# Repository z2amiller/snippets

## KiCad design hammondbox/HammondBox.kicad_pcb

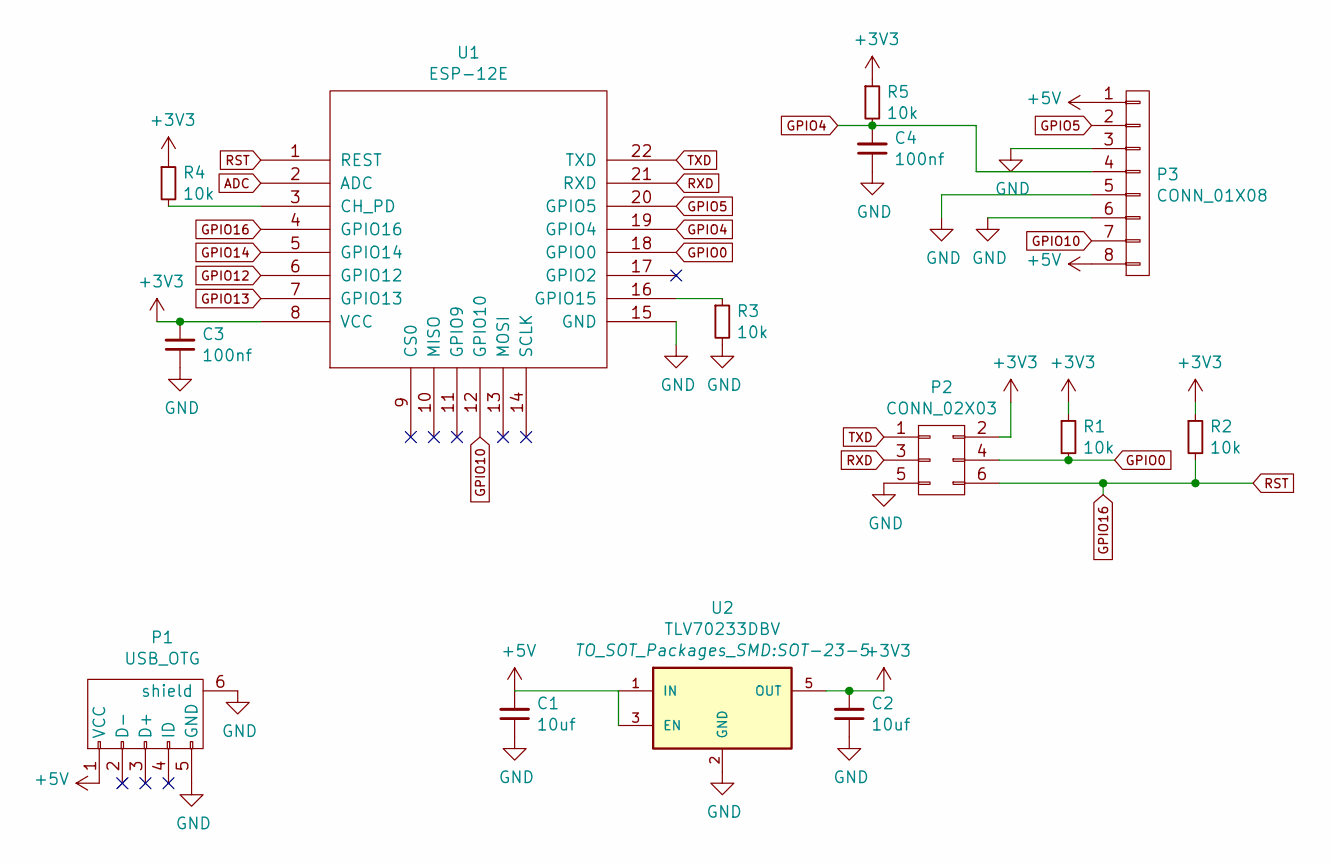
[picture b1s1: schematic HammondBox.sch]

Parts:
C1, C2: 10uf; C_0805_HandSoldering
C3, C4: 100nf; C_0603_HandSoldering
P1: USB_OTG; USB_Micro-B
P2: CONN_02X03; Pin_Header_Straight_2x03
P3: CONN_01X08; Pin_Header_Straight_1x08
R1, R2, R3, R4, R5: 10k; R_0603_HandSoldering
U1: ESP-12E
U2: TLV70233DBV; SOT-23-5

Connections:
+3V3: C2.2, C3.2, P2.2, R1.1, R2.1, R4.1, R5.1, U1.8 (VCC), U2.5 (OUT)
+5V: C1.2, P1.1 (VCC), P3.1, P3.8, U2.1 (IN), U2.3 (EN)
ADC: U1.2 (ADC)
GND: C1.1, C2.1, C3.1, C4.1, P1.5 (GND), P1.6 (shield), P2.5, P3.3, P3.5, P3.6, R3.2, U1.15 (GND), U2.2 (GND)
GPIO0: P2.4, R1.2, U1.18 (GPIO0)
GPIO4: C4.2, P3.4, R5.2, U1.19 (GPIO4)
GPIO5: P3.2, U1.20 (GPIO5)
GPIO10: P3.7, U1.12 (GPIO10)
GPIO12: U1.6 (GPIO12)
GPIO13: U1.7 (GPIO13)
GPIO14: U1.5 (GPIO14)
GPIO16: P2.6, R2.2, U1.1 (REST), U1.4 (GPIO16)
unnamed: R3.1, U1.16 (GPIO15)
unnamed: R4.2, U1.3 (CH_PD)
RXD: P2.3, U1.21 (RXD)
TXD: P2.1, U1.22 (TXD)

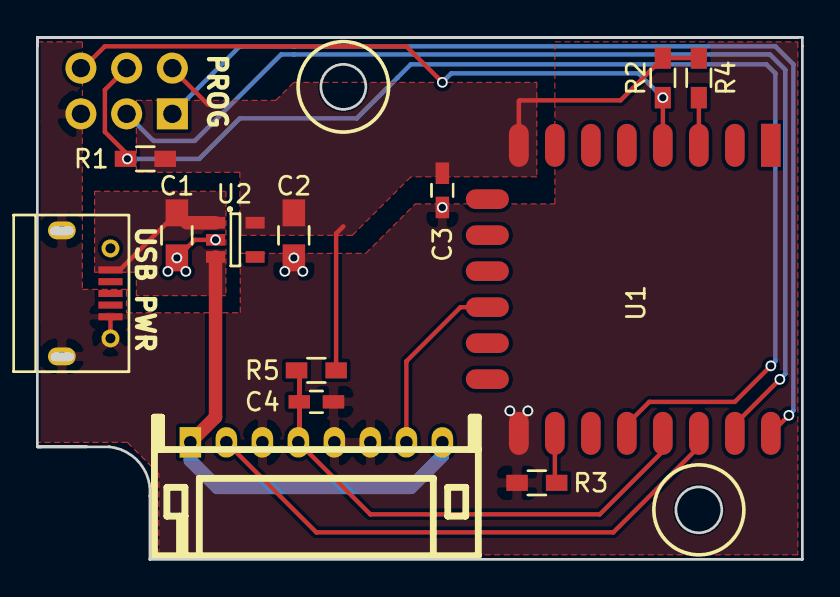
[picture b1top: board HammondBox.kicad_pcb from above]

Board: 2 copper layers, 42.1 x 28.7 mm, 14 parts (1 on the bottom side), 12 nets.

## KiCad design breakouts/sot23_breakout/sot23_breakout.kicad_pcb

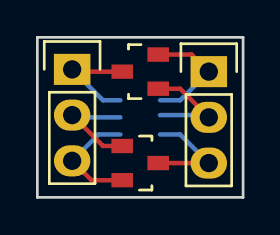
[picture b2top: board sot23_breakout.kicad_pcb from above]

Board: 2 copper layers, 11.4 x 8.9 mm, 5 parts (1 on the bottom side), 6 nets.

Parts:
IC1: ATTINY10-TS; SOT-23-6
P1, P2: CONN_01X03; Pin_Header_Straight_1x03
Q1, Q2: MMBT3904; SOT-23

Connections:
LEFT_1: IC1.3, P1.1, Q2.3
LEFT_2: IC1.2, P1.2, Q1.1
LEFT_3: IC1.1, P1.3, Q1.2
RIGHT_1: IC1.4, P2.1, Q2.2
RIGHT_2: IC1.5, P2.2, Q2.1
RIGHT_3: IC1.6, P2.3, Q1.3

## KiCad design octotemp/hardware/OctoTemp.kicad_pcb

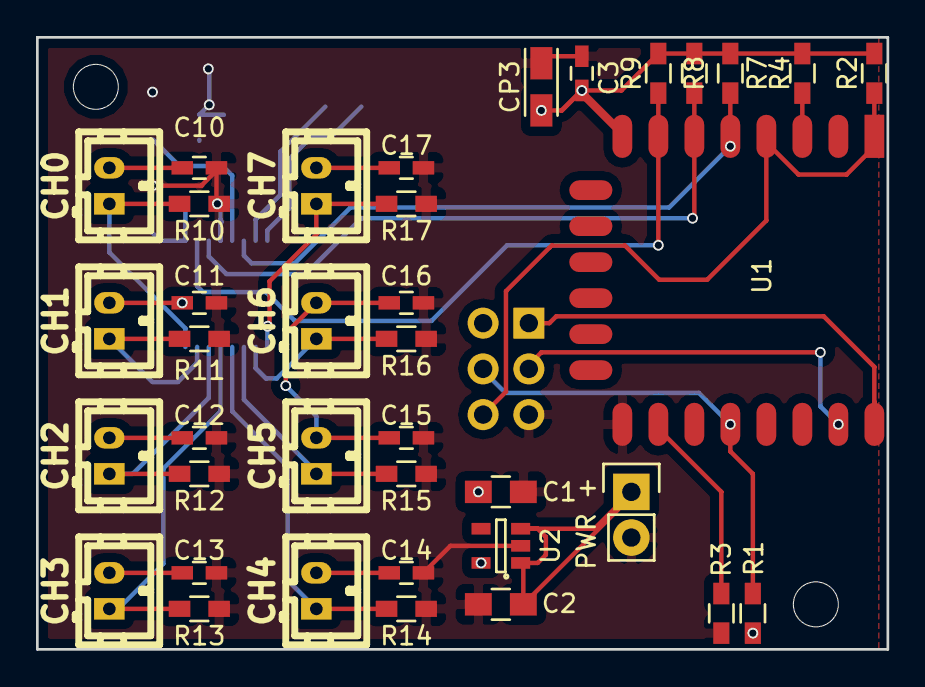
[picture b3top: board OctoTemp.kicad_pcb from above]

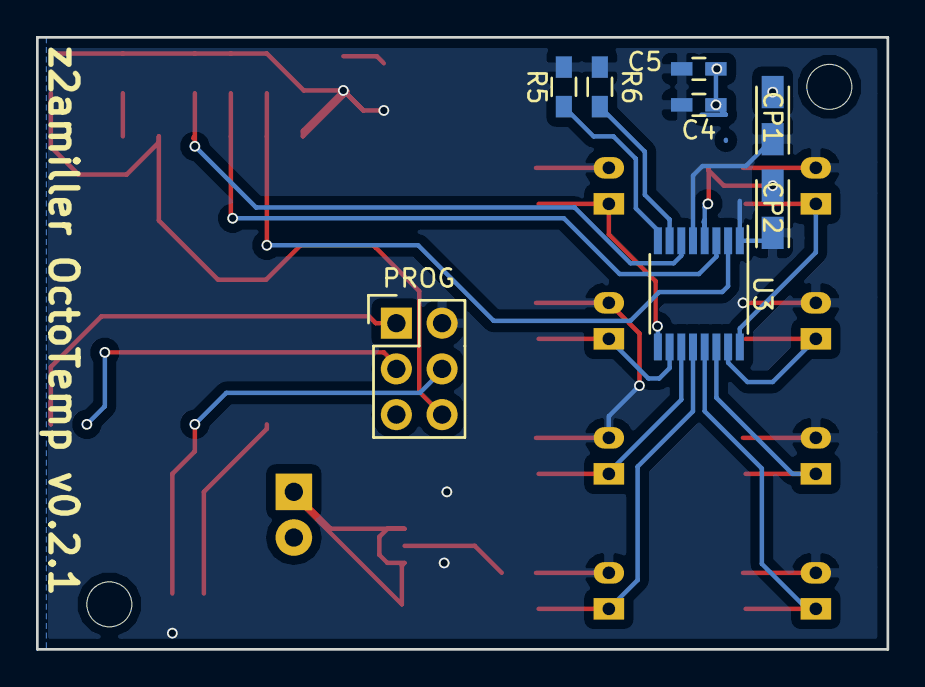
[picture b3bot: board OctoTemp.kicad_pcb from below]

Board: 2 copper layers, 47.2 x 34.0 mm, 46 parts (8 on the bottom side), 22 nets.

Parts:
C1, C2: 10uf; C_0805_HandSoldering
C3, C4, C5, C10, C11, C12, C13, C14, C15, C16, C17: 100nf; C_0603_HandSoldering
CH0, CH1, CH2, CH3, CH4, CH5, CH6, CH7: CONN_01X02; b2b-ph-kl
CP1, CP2, CP3: 1uf; TantalC_SizeA_EIA-3216_Reflow
PROG: CONN_02X03; Pin_Header_Straight_2x03
PWR +: CONN_01X02; Pin_Header_Straight_1x02
R1, R2, R3, R4, R5, R6, R7, R8, R9, R10, R11, R12, R13, R14, R15, R16, R17: 10k; R_0603_HandSoldering
U1: ESP-12E
U2: SPX3819M5; SOT-23-5
U3: ADC128D818; TSSOP-16_4.4x5mm_Pitch0.65mm

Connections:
+5V: C2.2, PWR +.1, U2.1, U2.3
ADC_GND: C1.2, C2.1, C3.1, C4.1, C5.2, C10.1, C11.1, C12.1, C13.1, C14.1, C15.1, C16.1, C17.1, CP1.2, CP2.2, CP3.1, PROG.5, PWR +.2, R3.2, R10.2, R11.2, R12.2, R13.2, R14.2, R15.2, R16.2, R17.2, U1.15, U2.2, U3.4
ADC_INT: R7.2, U1.5, U3.6
ADC_VIN: C1.1, C3.2, C4.2, C5.1, C10.2, C11.2, C12.2, C13.2, C14.2, C15.2, C16.2, C17.2, CH0.2, CH1.2, CH2.2, CH3.2, CH4.2, CH5.2, CH6.2, CH7.2, CP1.1, CP2.1, CP3.2, PROG.2, R1.1, R2.1, R4.1, R5.1, R6.1, R7.1, R8.1, R9.1, U1.8, U2.5, U3.1, U3.5
ESP_RST: PROG.6, R2.2, U1.1, U1.4
ESP_RXD: PROG.3, U1.21
ESP_TXD: PROG.1, U1.22
GPIO0: PROG.4, R1.2, U1.18
IN0: CH0.1, R10.1, U3.16
IN1: CH1.1, R11.1, U3.15
IN2: CH2.1, R12.1, U3.14
IN3: CH3.1, R13.1, U3.13
IN4: CH4.1, R14.1, U3.12
IN5: CH5.1, R15.1, U3.11
IN6: CH6.1, R16.1, U3.10
IN7: CH7.1, R17.1, U3.9
unnamed: R3.1, U1.16
unnamed: R4.2, U1.3
unnamed: R5.2, U3.8
unnamed: R6.2, U3.7
SCL: R8.2, U1.6, U3.3
SDA: R9.2, U1.7, U3.2

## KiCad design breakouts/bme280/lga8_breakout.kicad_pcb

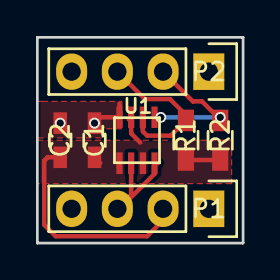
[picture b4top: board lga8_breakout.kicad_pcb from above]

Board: 2 copper layers, 11.4 x 11.4 mm, 7 parts (0 on the bottom side), 4 nets.

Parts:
C1, C2: 100nf; C_0603_HandSoldering
P1, P2: CONN_01X04; Pin_Header_Straight_1x04
R1, R2: 10k; R_0603_HandSoldering
U1: BME280; FGA8

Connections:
+3V3: C1.1, C2.2, P1.2, R1.1, R2.1, U1.2, U1.6, U1.8
GND: C1.2, C2.1, P1.3, U1.1, U1.5, U1.7
unnamed: P2.2, R2.2, U1.4
unnamed: P2.3, R1.2, U1.3

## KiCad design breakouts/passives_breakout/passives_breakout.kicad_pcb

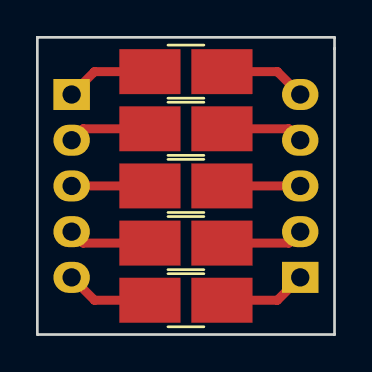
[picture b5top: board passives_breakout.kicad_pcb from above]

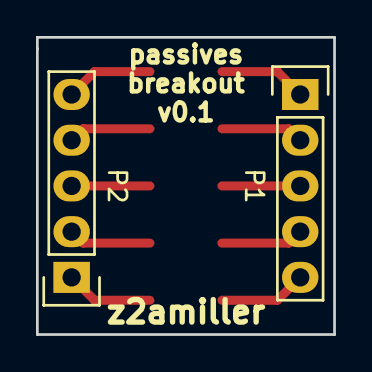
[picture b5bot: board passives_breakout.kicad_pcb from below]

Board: 2 copper layers, 16.5 x 16.5 mm, 7 parts (2 on the bottom side), 10 nets.

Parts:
P1, P2: CONN_01X05; Pin_Header_Straight_1x05
R1, R2, R3, R4, R5: R_Small; R_1210_HandSoldering

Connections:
unnamed: P1.1, R5.2
unnamed: P1.2, R4.2
unnamed: P1.3, R3.2
unnamed: P1.4, R2.2
unnamed: P1.5, R1.2
unnamed: P2.1, R1.1
unnamed: P2.2, R2.1
unnamed: P2.3, R3.1
unnamed: P2.4, R4.1
unnamed: P2.5, R5.1

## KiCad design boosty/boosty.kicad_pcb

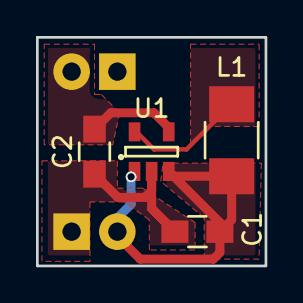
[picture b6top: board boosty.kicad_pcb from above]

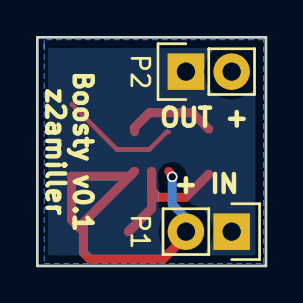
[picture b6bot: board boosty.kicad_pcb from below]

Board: 2 copper layers, 12.7 x 12.7 mm, 6 parts (2 on the bottom side), 4 nets.

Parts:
C1, C2: 10uF; C_0805_HandSoldering
L1: 4.7uH; R_1210_HandSoldering
P1, P2: CONN_01X02; Pin_Header_Straight_1x02
U1: XC9140; SOT-23-5

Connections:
+5V: C2.1, P2.2, U1.4
+BATT: C1.1, L1.1, P1.2, U1.1, U1.3
GND: C1.2, C2.2, P1.1, P2.1, U1.2
unnamed: L1.2, U1.5

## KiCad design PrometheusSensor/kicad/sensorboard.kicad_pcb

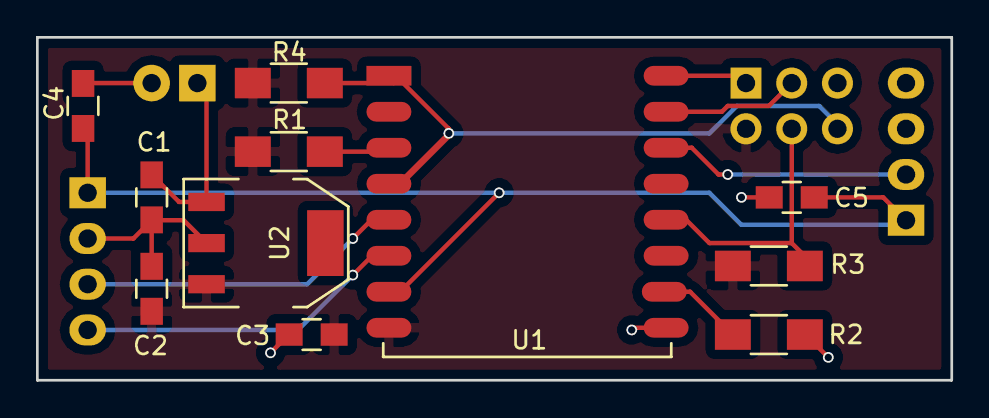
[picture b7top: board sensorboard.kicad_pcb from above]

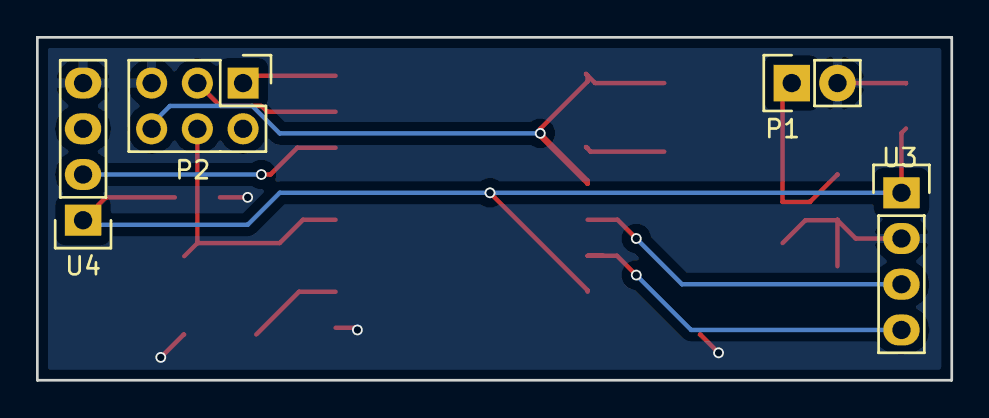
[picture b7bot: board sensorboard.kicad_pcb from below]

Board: 2 copper layers, 50.8 x 19.0 mm, 15 parts (4 on the bottom side), 13 nets.

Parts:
C1, C2: 10uf; C_0805_HandSoldering
C3, C4, C5: 100nf; C_0805_HandSoldering
P1: PWR; Pin_Header_Straight_1x02
P2: PROG; Pin_Header_Straight_2x03
R1, R2, R3, R4: 10k; R_1206_HandSoldering
U1: ESP-07v2; ESP-12
U2: TC1262; SOT-223
U3: BMP180_board; Pin_Header_Straight_1x04
U4: DHT22; Pin_Header_Straight_1x04

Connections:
+3.3VP: C4.2, C5.2, U1.7, U3.1, U4.1
+3V3: C2.1, C3.1, P2.2, R1.1, R3.1, R4.1, U1.8, U2.3
+6V: C1.1, P1.1, U2.1
CH_PD: R1.2, U1.3
GND: C1.2, C2.2, C3.2, C4.1, C5.1, P1.2, P2.5, R2.2, U1.9, U2.2, U3.2, U4.4
GPIO0: P2.4, R3.2, U1.12
GPIO4: U1.14, U4.2
GPIO12: U1.6, U3.4
GPIO14: U1.5, U3.3
GPIO15: R2.1, U1.10
GPIO16: P2.6, R4.2, U1.1, U1.4
RXD: P2.3, U1.15
TXD: P2.1, U1.16

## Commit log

2015-08-05 Initial checkin of mFi "code" to snippets.
2015-08-05 Remove README header.
2015-08-06 Initial commit of ladybug board.
2015-08-07 Fixed ground plane and drill holes.
2015-08-09 Some prometheus support and config files.
2015-08-09 Change label of scraped nodes.
2015-08-12 Send sensor data to prometheus from an esp8266
2015-09-21 Add bmp180 board
2015-09-21 KiCad files for PrometheusSensor
2015-09-21 Centralize PrometheusSensor code
2015-09-21 Clean up comments and formatting.
2015-10-17 Move ladybug files to dedicated repository.
2015-10-17 Moved sensor to a dedicated repository.
2015-10-31 Quickie breakout for sot-23 and sot-23-5.
2015-11-01 8 x temperature sensor for esp8266.
2015-11-02 Rearrange board to fit properly in Hammond 1551L.
2015-11-02 Fix board outline - try, try again.
2015-11-16 Boost converter board based on XC9401.
2015-11-16 Simple breakout for passives.
2015-11-24 Some test code for octotemp using the TI128d818.
2015-11-24 Some quick code cleanups.
2015-11-24 Fix programming header and reset.
2015-12-17 Octotemp board with 2 1x8 pin JST connectors.
2015-12-17 Fixed silkscreening.
2015-12-17 Added name/version silkscreening.
2016-02-21 Use prometheus client to send messages.
2016-02-22 A mostly-working OctoTemp
2016-02-22 Use the new MapMetric
2016-02-22 Fix OctoTemp, set up to use esp8266 2.0.1-rc2
2016-02-22 TODO -> Done
2016-02-22 Added a constraint on tempC
2016-02-23 Use the new adc128d818 library.
2016-02-29 Increased the drill sizes of the JST connectors
2016-02-29 Initialize the wire library explicitly.
2016-03-20 Create a breakout for the BME280
2016-03-20 Why didn't I make this sot23-6 in the first place?
2016-03-20 Larger pads, better soldermask
2016-04-11 ESP8266 neopixel driver in a Hammond 1551H box.
2016-04-11 Fix some silkscreens.
2016-04-22 Replace oval drills with edgecut slots for OSHPark
2016-04-22 Increase 5v zone size
2016-05-08 Don't use GPIO10 which apparently is reserved.
2016-07-09 Use MCP1702 for regulator, use reflow sized pads.
2016-07-09 No gerbers
